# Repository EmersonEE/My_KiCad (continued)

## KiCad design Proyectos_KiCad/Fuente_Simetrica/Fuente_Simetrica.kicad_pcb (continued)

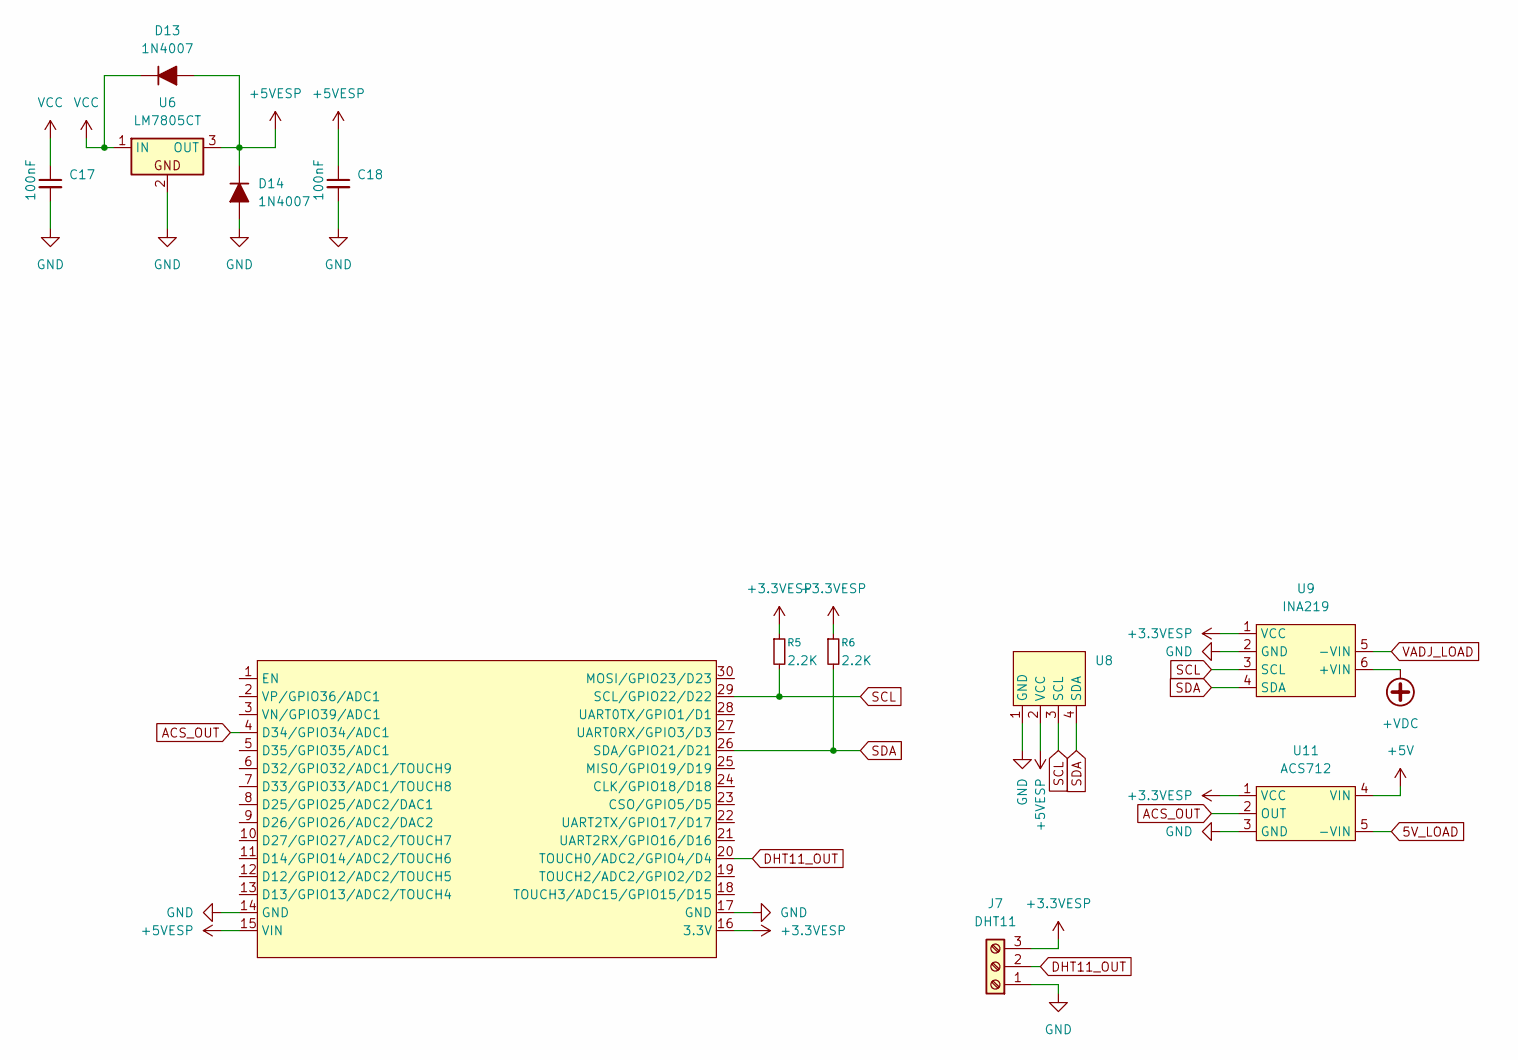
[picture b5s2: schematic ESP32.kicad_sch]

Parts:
C17, C18: 100nF; C_Disc_D3.0mm_W2.0mm_P2.50mm
D13, D14: 1N4007; D_SMA
J7: DHT11; PinHeader_1x03_P2.54mm_Vertical
R5, R6: 2.2K
U6: LM7805CT; TO-220-3_Vertical
U7: ESP32_DevKit_V1_DOIT; ESP32_DEVKIT_V1_E32
U8: SSD1306
U9: INA219; INA219_Module
U11: ACS712; ACS712-20A

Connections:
5V_LOAD: U11.5 (-VIN); also elsewhere on the board
+3.3VESP: J7.3, R5.1, R6.1, U7.16 (3.3V), U9.1 (VCC), U11.1 (VCC)
+5V: U11.4 (VIN); also elsewhere on the board
+5VESP: C18.1, D13.2 (A), D14.1 (K), U6.3 (OUT), U7.15 (VIN), U8.2 (VCC)
+VDC: U9.6 (+VIN); also elsewhere on the board
ACS_OUT: U7.4 (D34/GPIO34/ADC1), U11.2 (OUT)
DHT11_OUT: J7.2, U7.20 (TOUCH0/ADC2/GPIO4/D4)
GND: C17.2, C18.2, D14.2 (A), J7.1, U6.2, U7.14 (GND), U7.17 (GND), U8.1 (GND), U9.2 (GND), U11.3 (GND); also elsewhere on the board
SCL: R5.2, U7.29 (SCL/GPIO22/D22), U8.3 (SCL), U9.3 (SCL)
SDA: R6.2, U7.26 (SDA/GPIO21/D21), U8.4 (SDA), U9.4 (SDA)
VADJ_LOAD: U9.5 (-VIN); also elsewhere on the board
VCC: C17.1, D13.1 (K), U6.1 (IN); also elsewhere on the board

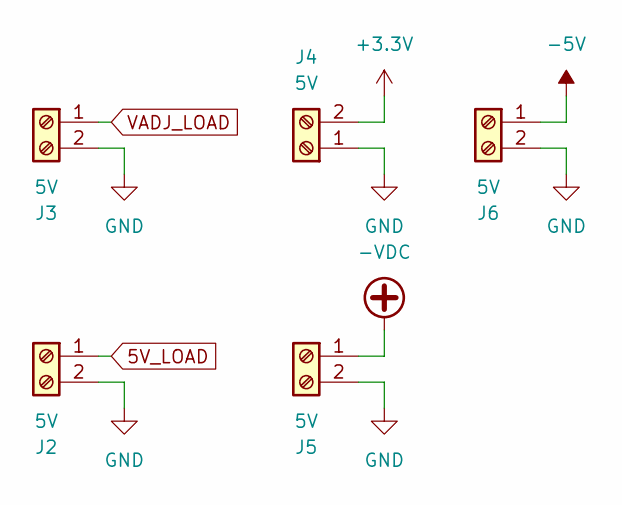
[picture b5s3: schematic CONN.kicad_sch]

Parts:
J2, J3, J4, J5, J6: 5V; Molex_KK-254_AE-6410-02A_1x02_P2.54mm_Vertical

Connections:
5V_LOAD: J2.1; also elsewhere on the board
+3.3V: J4.2; also elsewhere on the board
-5V: J6.1; also elsewhere on the board
-VDC: J5.1; also elsewhere on the board
GND: J2.2, J3.2, J4.1, J5.2, J6.2; also elsewhere on the board
VADJ_LOAD: J3.1; also elsewhere on the board

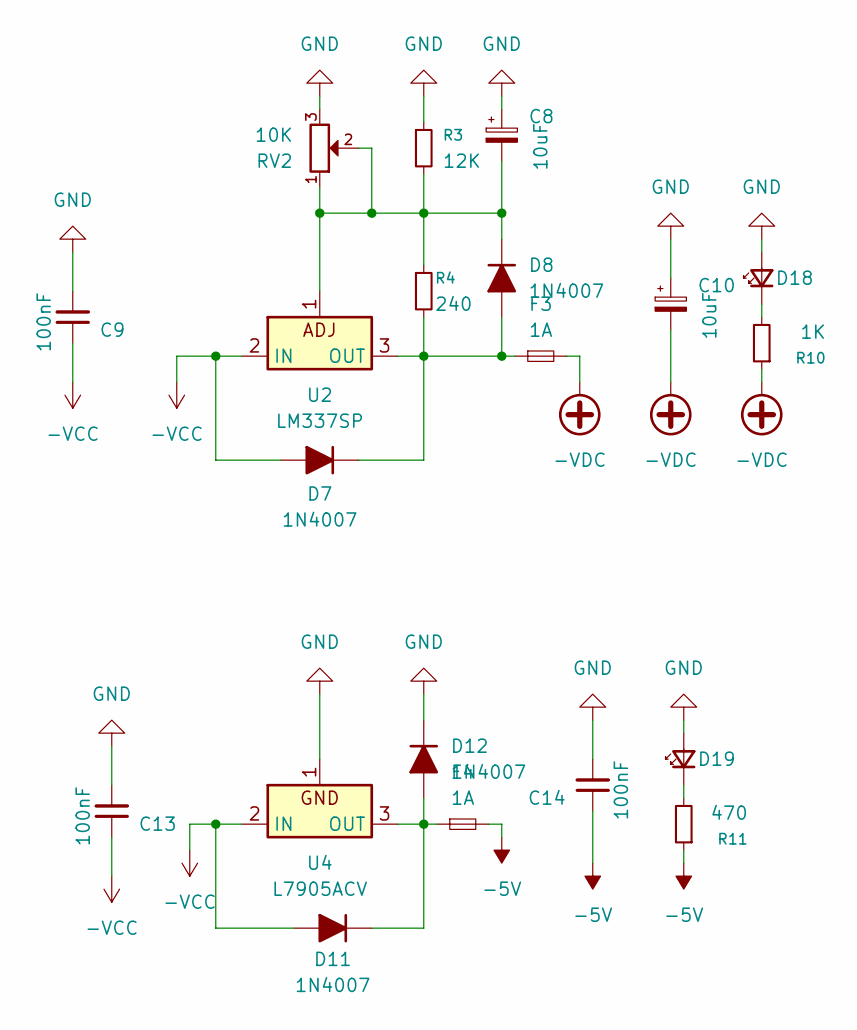
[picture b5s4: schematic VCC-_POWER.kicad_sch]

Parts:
C8, C10: 10uF; CP_Radial_D5.0mm_P2.50mm
C9, C13, C14: 100nF; C_Disc_D3.0mm_W2.0mm_P2.50mm
D7, D11: 1N4007; D_SMA
D8, D12: 1N4007; D_DO-41_SOD81_P7.62mm_Horizontal
D18, D19: LED_D5.0mm
F3, F4: 1A; Fuse_5x22mm
R3: 12K; 220
R4: 240; 220
R10: 1K
R11: 470
RV2: 10K; Molex_KK-254_AE-6410-03A_1x03_P2.54mm_Vertical
U2: LM337SP; TO-220-3_Vertical
U4: L7905ACV; TO-220-3_Vertical

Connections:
-5V: C14.1, F4.2, R11.1; also elsewhere on the board
-VCC: C9.1, C13.1, D7.2 (A), D11.2 (A), U2.2 (IN), U4.2 (IN); also elsewhere on the board
-VDC: C10.2, F3.2, R10.1; also elsewhere on the board
GND: C8.1, C9.2, C10.1, C13.2, C14.2, D12.1 (K), D18.2 (A), D19.2 (A), R3.1, RV2.3, U4.1; also elsewhere on the board
unnamed: D7.1 (K), D8.2 (A), F3.1, R4.2, U2.3 (OUT)
unnamed: C8.2, D8.1 (K), R3.2, R4.1, RV2.1, RV2.2, U2.1
unnamed: D11.1 (K), D12.2 (A), F4.1, U4.3 (OUT)
unnamed: D18.1 (K), R10.2
unnamed: D19.1 (K), R11.2

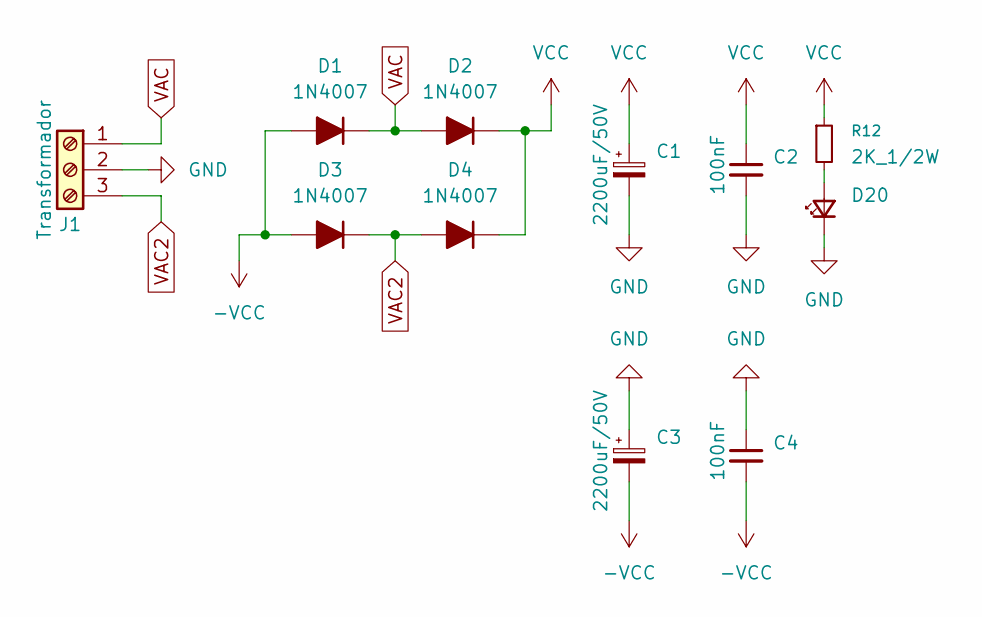
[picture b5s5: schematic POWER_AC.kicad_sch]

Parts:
C1, C3: 2200uF/50V; CP_Radial_D17.0mm_P7.50mm
C2, C4: 100nF; C_Disc_D3.0mm_W2.0mm_P2.50mm
D1, D2, D3, D4: 1N4007; D_A-405_P10.16mm_Horizontal
D20: LED_D5.0mm
J1: Transformador; TerminalBlock_Phoenix_MKDS-1,5-3-5.08_1x03_P5.08mm_Horizont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
R12: 2K_1/2W; R_Axial_DIN0207_L6.3mm_D2.5mm_P10.16mm_Horizontal

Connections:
-VCC: C3.2, C4.2, D1.2 (A), D3.2 (A); also elsewhere on the board
GND: C1.2, C2.2, C3.1, C4.1, D20.1 (K), J1.2; also elsewhere on the board
unnamed: D20.2 (A), R12.2
VAC: D1.1 (K), D2.2 (A), J1.1
VAC2: D3.1 (K), D4.2 (A), J1.3
VCC: C1.1, C2.1, D2.1 (K), D4.1 (K), R12.1; also elsewhere on the board

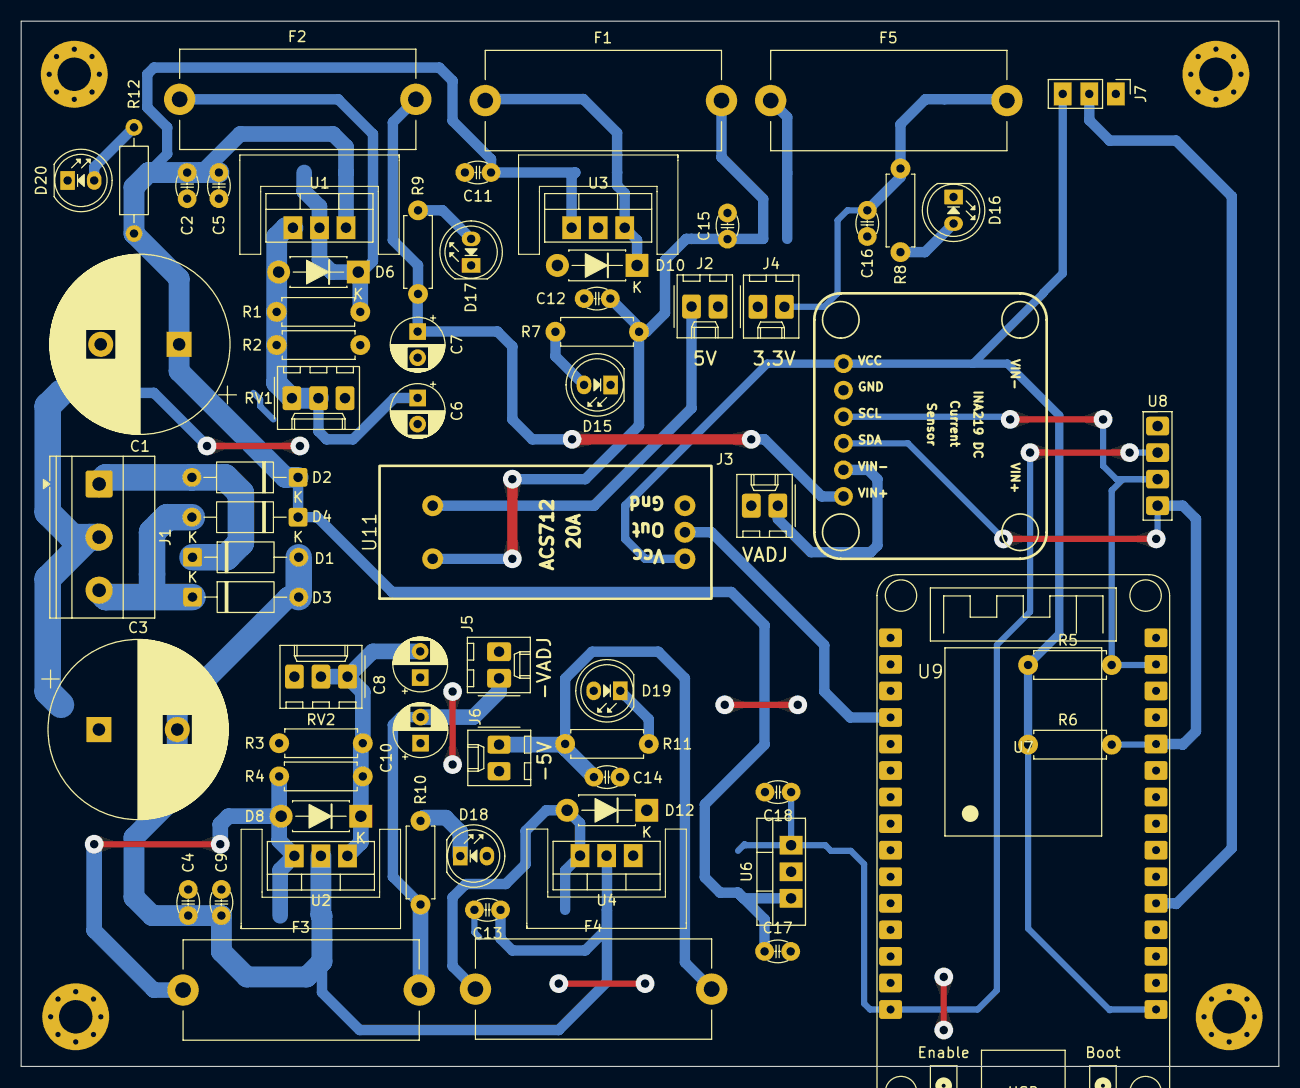
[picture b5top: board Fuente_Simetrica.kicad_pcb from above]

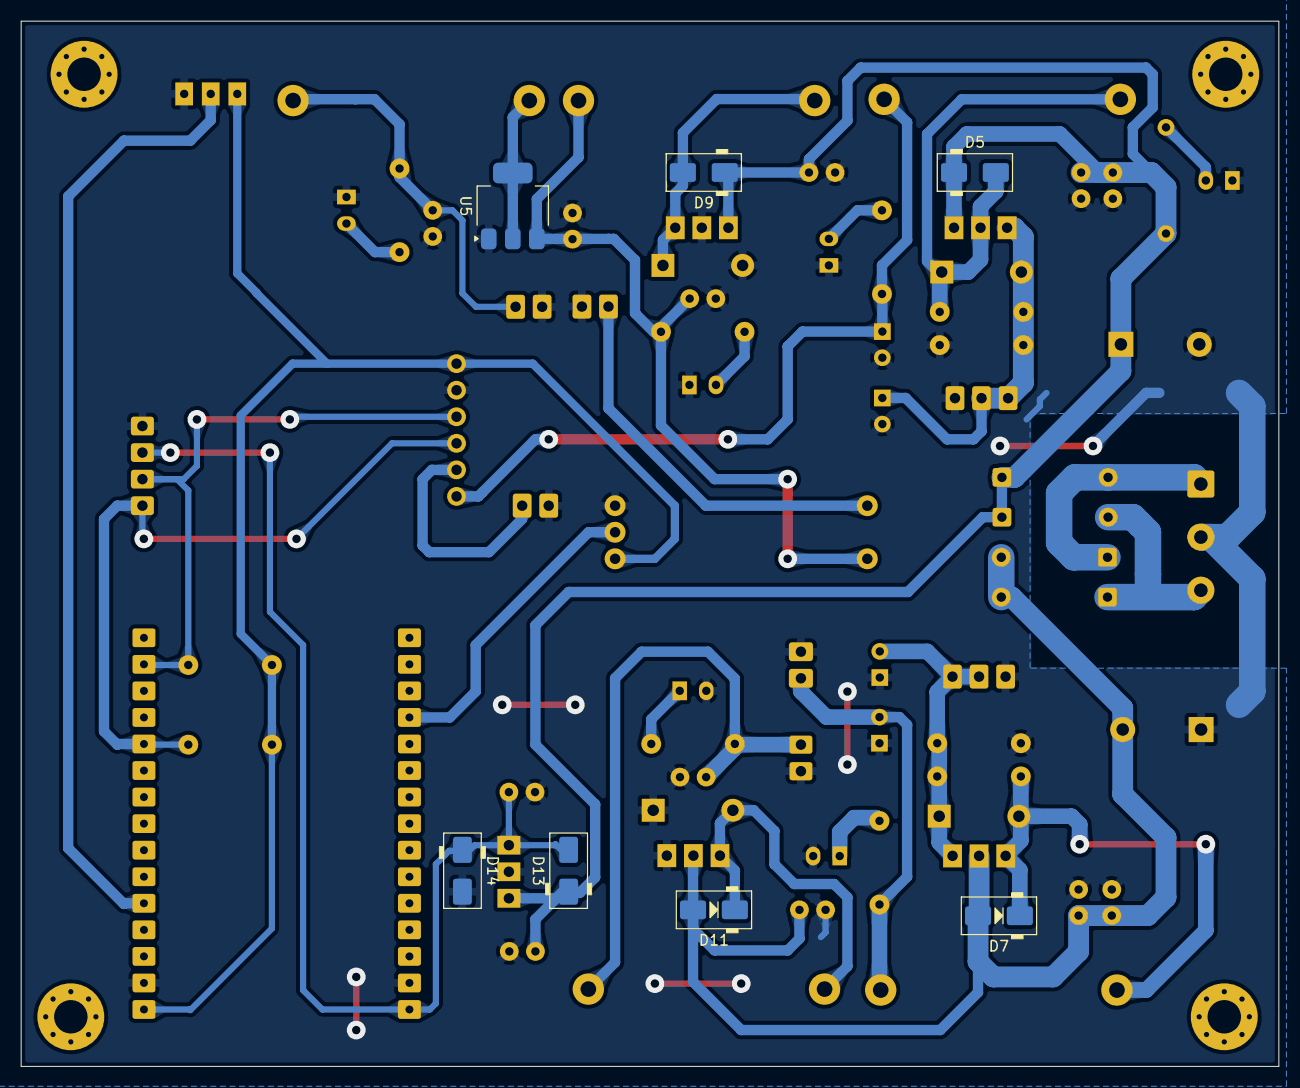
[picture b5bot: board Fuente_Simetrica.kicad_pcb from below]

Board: 2 copper layers, 120.3 x 100.0 mm, 74 parts (7 on the bottom side), 31 nets.

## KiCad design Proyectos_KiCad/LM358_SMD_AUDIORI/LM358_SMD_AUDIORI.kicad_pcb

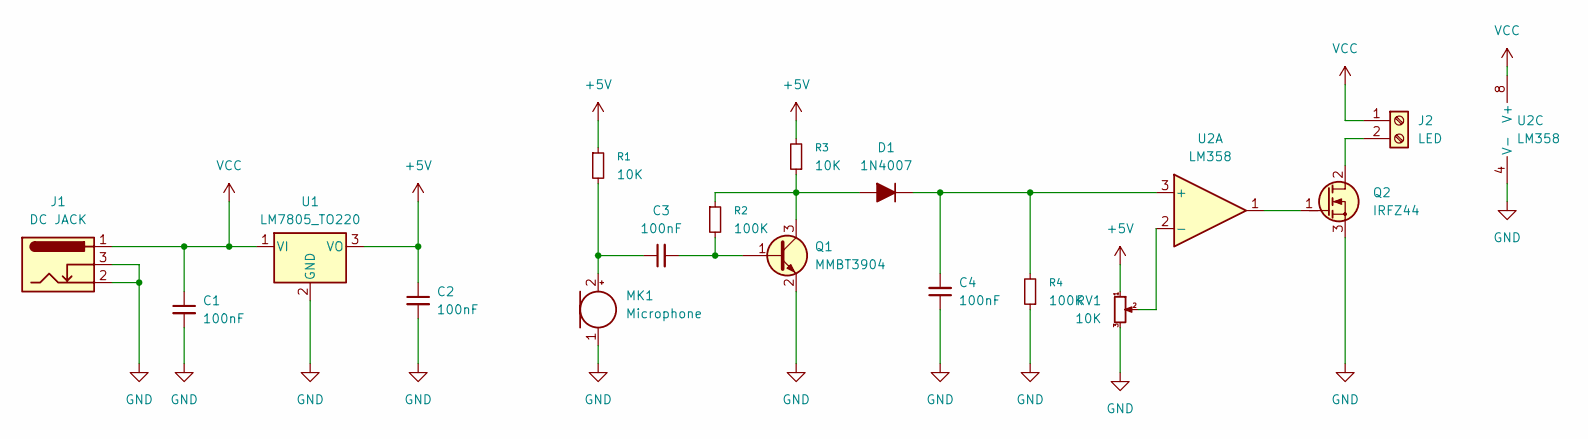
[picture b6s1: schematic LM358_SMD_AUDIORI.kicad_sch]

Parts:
C1, C2, C3, C4: 100nF; C_Disc_D3.8mm_W2.6mm_P2.50mm
D1: 1N4007; D_DO-41_SOD81_P7.62mm_Horizontal
J1: DC JACK; BarrelJack_Horizontal
J2: LED; TerminalBlock_Phoenix_MKDS-3-2-5.08_1x02_P5.08mm_Horizontal
MK1: Microphone; POM-2244P-C3310-2-R
Q1: MMBT3904; SOT-23
Q2: IRFZ44; TO-220-3_Vertical_GDS
R1, R3: 10K; R_0805_2012Metric_Pad1.15x1.40mm
R2, R4: 100K; R_0805_2012Metric_Pad1.15x1.40mm
RV1: 10K; Potentiometer_Runtron_RM-065_Vertical
U1: LM7805_TO220; TO-220-3_Horizontal_TabDown
U2: LM358; SO-8_3.9x4.9mm_P1.27mm

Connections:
+5V: C2.1, R1.1, R3.2, RV1.1, U1.3 (VO)
GND: C1.2, C2.2, C4.1, J1.2, J1.3, MK1.1 (-), Q1.2 (E), Q2.3 (S), R4.1, RV1.3, U1.2 (GND), U2.4 (V-)
unnamed: D1.2 (A), Q1.3 (C), R2.1, R3.1
unnamed: C4.2, D1.1 (K), R4.2, U2.3 (+)
unnamed: J2.2, Q2.2 (D)
unnamed: C3.1, MK1.2 (+), R1.2
unnamed: C3.2, Q1.1 (B), R2.2
unnamed: Q2.1 (G), U2.1
unnamed: RV1.2, U2.2 (-)
VCC: C1.1, J1.1, J2.1, U1.1 (VI), U2.8 (V+)

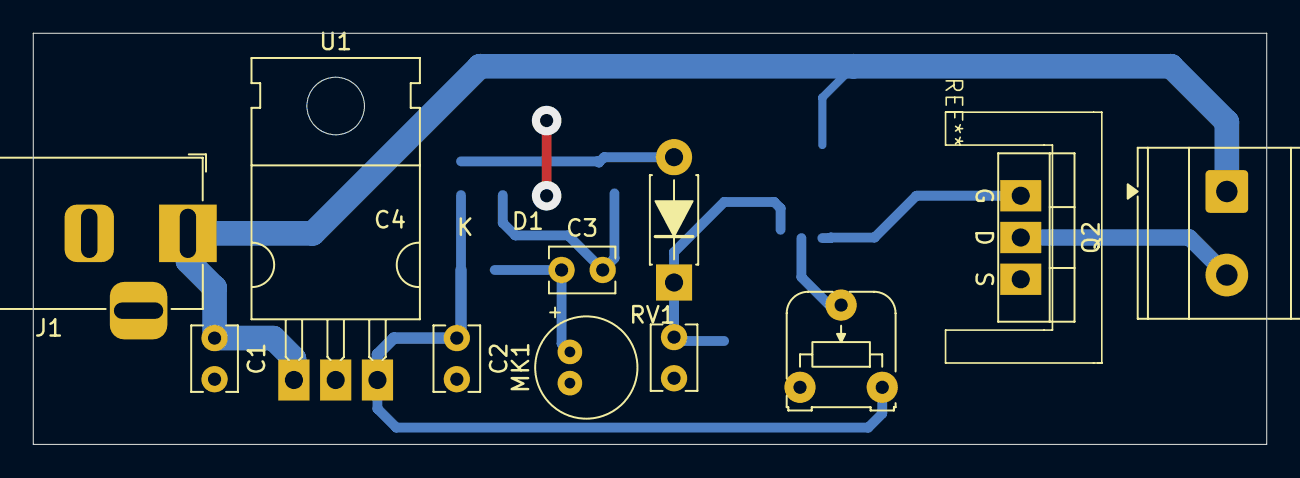
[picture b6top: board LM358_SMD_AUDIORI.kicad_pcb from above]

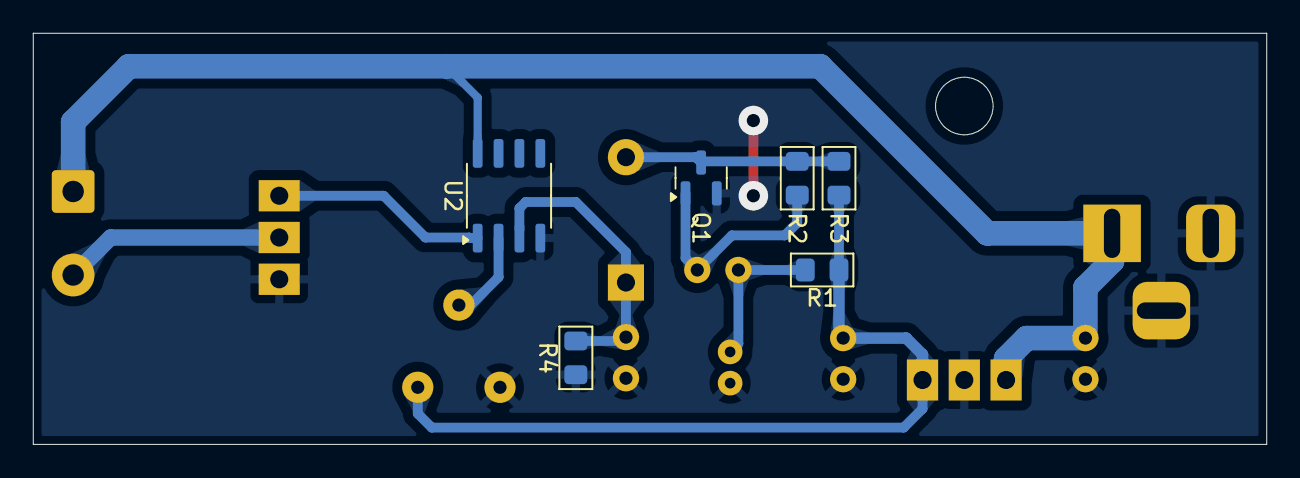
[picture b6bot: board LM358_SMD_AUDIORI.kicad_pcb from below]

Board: 2 copper layers, 75.0 x 25.0 mm, 17 parts (6 on the bottom side), 10 nets.

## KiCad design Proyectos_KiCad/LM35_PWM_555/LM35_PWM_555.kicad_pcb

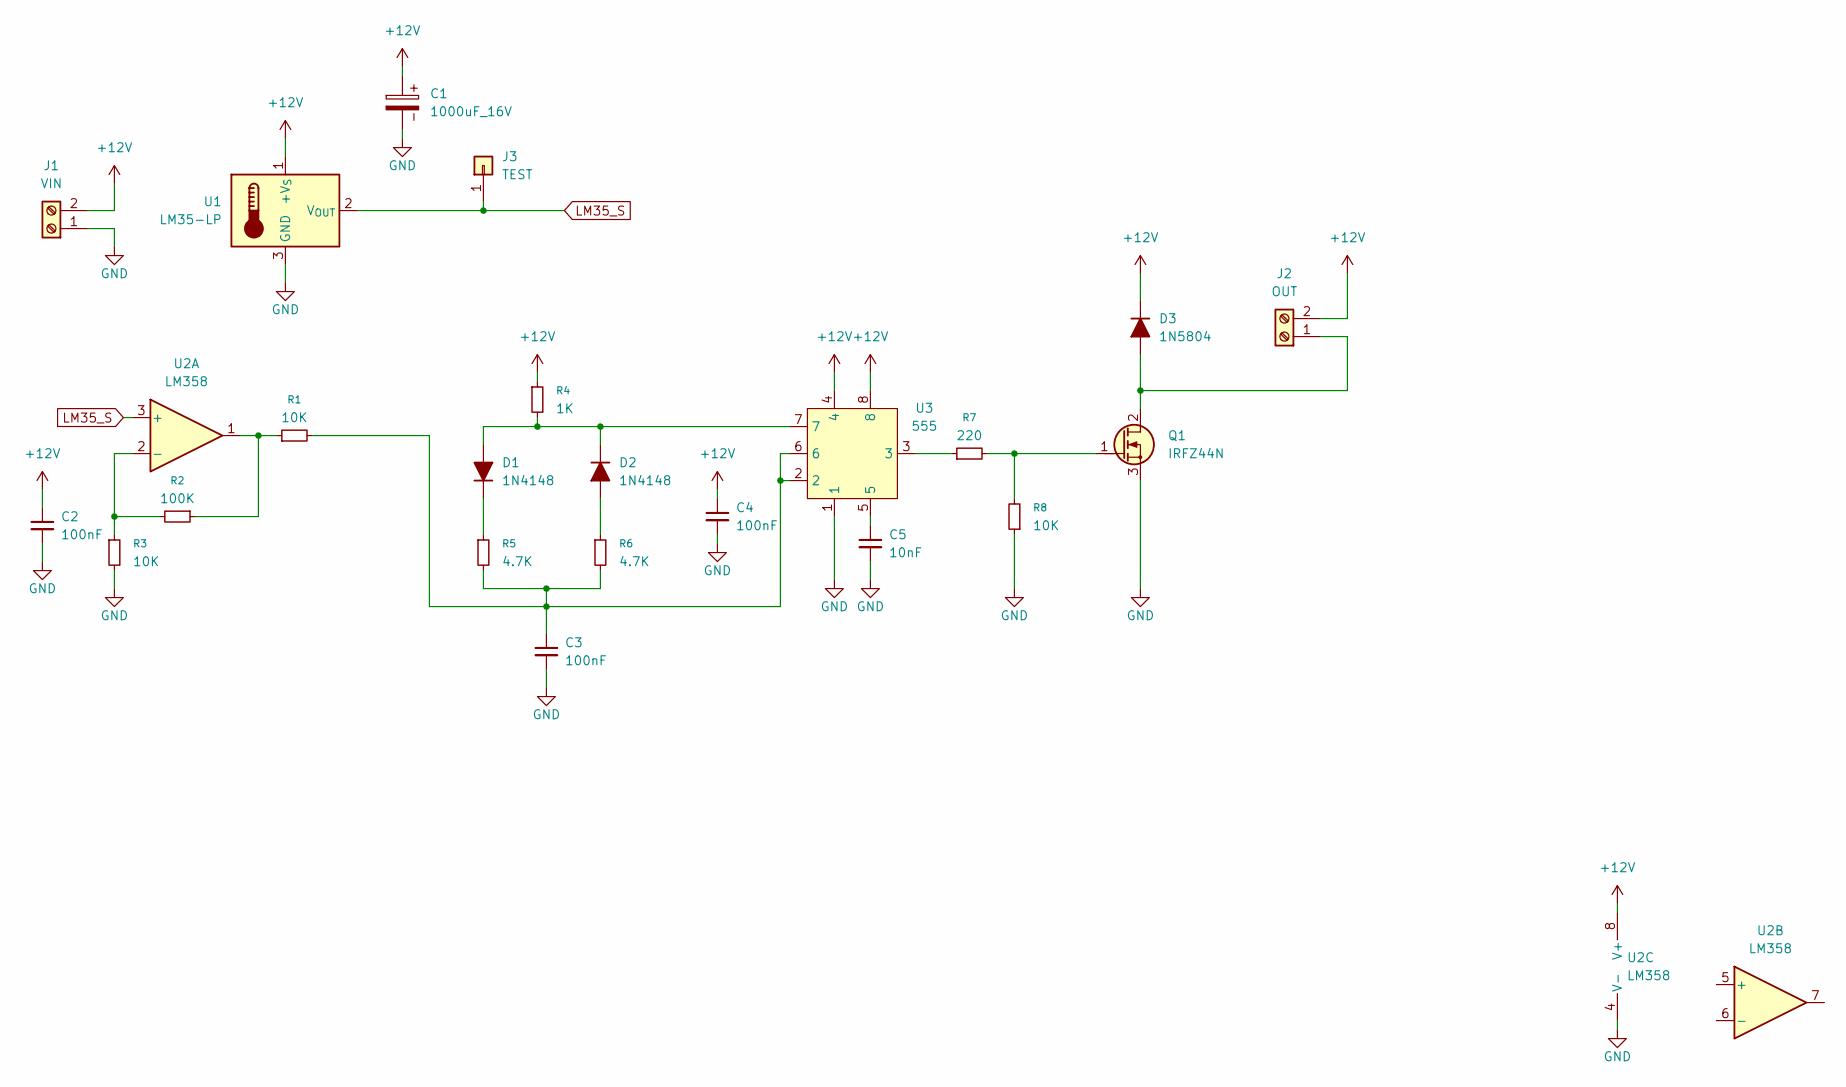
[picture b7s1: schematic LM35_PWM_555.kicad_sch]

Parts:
C1: 1000uF_16V; CP_Radial_D10.0mm_P5.00mm
C2, C3, C4: 100nF; C_Disc_D7.0mm_W2.5mm_P5.00mm
C5: 10nF; C_Disc_D7.0mm_W2.5mm_P5.00mm
D1, D2: 1N4148; D_DO-35_SOD27_P10.16mm_Horizontal
D3: 1N5804; D_A-405_P10.16mm_Horizontal
J1: VIN; TerminalBlock_CUI_TB007-508-02_1x02_P5.08mm_Horizontal
J2: OUT; TerminalBlock_CUI_TB007-508-02_1x02_P5.08mm_Horizontal
J3: TEST; PinHeader_1x01_P2.54mm_Vertical
Q1: IRFZ44N; TO-220-3_Vertical
R1, R3, R8: 10K
R2: 100K
R4: 1K
R5, R6: 4.7K
R7: 220
U1: LM35-LP; TO-92_Inline_Wide
U2: LM358; DIP-8_W7.62mm_LongPads
U3: 555; DIP-8_W7.62mm_LongPads

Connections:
+12V: C1.1, C2.1, C4.1, D3.1 (K), J1.2, J2.2, R4.1, U1.1 (+V_{S}), U2.8 (V+), U3.4, U3.8
GND: C1.2, C2.2, C3.2, C4.2, C5.2, J1.1, Q1.3 (S), R3.2, R8.1, U1.3 (GND), U2.4 (V-), U3.1
LM35_S: J3.1 (Pin_1_1), U1.2 (V_{OUT}), U2.3 (+)
unnamed: C3.1, R1.2, R5.2, R6.2, U3.2, U3.6
unnamed: C5.1, U3.5
unnamed: D1.2 (A), D2.1 (K), R4.2, U3.7
unnamed: D1.1 (K), R5.1
unnamed: D2.2 (A), R6.1
unnamed: D3.2 (A), J2.1, Q1.2 (D)
unnamed: Q1.1 (G), R7.2, R8.2
unnamed: R1.1, R2.1, U2.1
unnamed: R7.1, U3.3
unnamed: R2.2, R3.1, U2.2 (-)

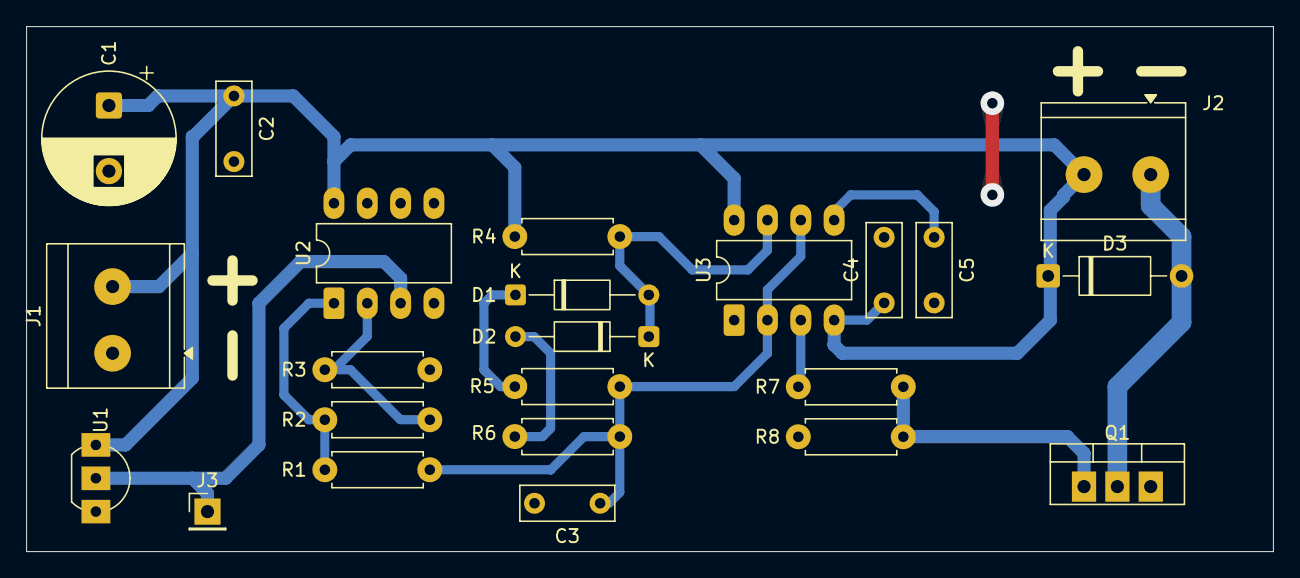
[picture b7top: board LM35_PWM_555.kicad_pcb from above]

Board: 2 copper layers, 95.0 x 40.0 mm, 23 parts (0 on the bottom side), 13 nets.
